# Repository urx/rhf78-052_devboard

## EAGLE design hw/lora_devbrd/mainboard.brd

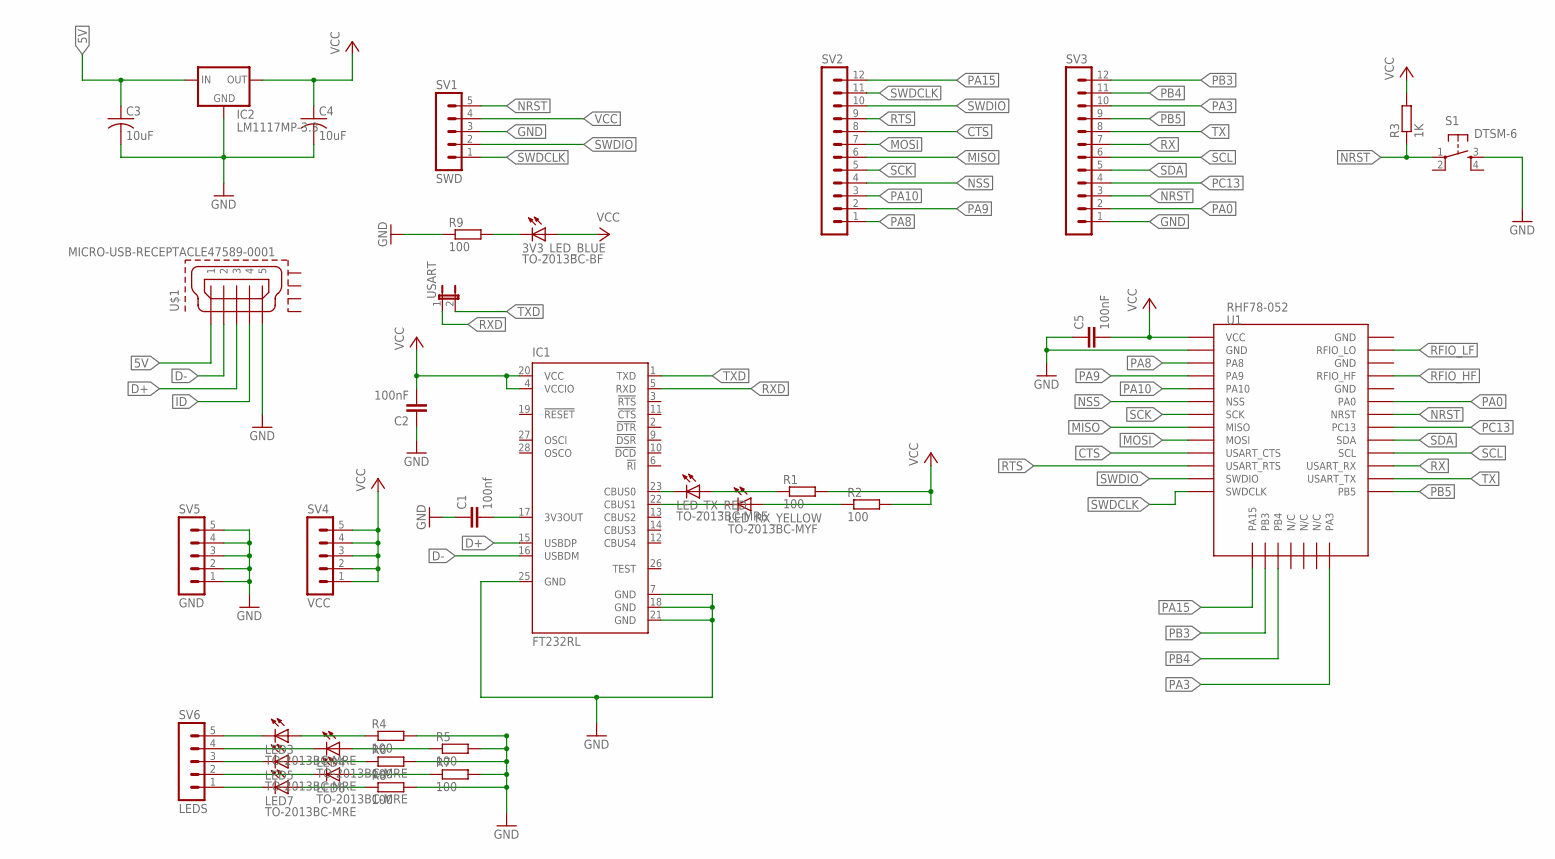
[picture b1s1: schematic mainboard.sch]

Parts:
3V3_LED_BLUE: TO-2013BC-BF; CHIPLED_1206
C1: 100nf; C1206
C2, C5: 100nF; C1206
C3, C4: 10uF; C1206
IC1: FT232RL; SSOP28
IC2: LM1117MP-3.3; SOT223
LED3, LED4, LED5, LED6, LED7: TO-2013BC-MRE; CHIPLED_1206
LED_RX_YELLOW: TO-2013BC-MYF; CHIPLED_1206
LED_TX_RED: TO-2013BC-MRE; CHIPLED_1206
R1, R2, R4, R5, R6, R7, R8, R9: 100; R1206
R3: 1K; R1206
S1: DTSM-6
SV1: SWD; MA05-1
SV2, SV3: MA12-1
SV4: VCC; MA05-1
SV5: GND; MA05-1
SV6: LEDS; MA05-1
U1: RHF78-052
U$1: MICRO-USB-RECEPTACLE47589-0001; 47589-0001
USART: JP1E; JP1

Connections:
3V3OUT: C1.2, IC1.17 (3V3OUT)
5V: C3.1, IC2.3 (IN), U$1.1
CBUS0: IC1.23 (CBUS0), LED_TX_RED.C
CBUS1: IC1.22 (CBUS1), LED_RX_YELLOW.C
CTS: SV2.8, U1.USART_CTS
D+: IC1.15 (USBDP), U$1.3
D-: IC1.16 (USBDM), U$1.2
GND: C1.1, C2.1, C3.2, C4.2, C5.1, IC1.7 (GND), IC1.18 (GND), IC1.21 (GND), IC1.25 (GND), IC2.1 (GND), R4.2, R5.2, R6.2, R7.2, R8.2, R9.1, S1.3, SV1.3, SV3.1, SV5.1, SV5.2, SV5.3, SV5.4, SV5.5, U1.GND@1 (GND), U1.GND@2 (GND), U1.GND@3 (GND), U1.GND@4 (GND), U$1.5
ID: U$1.4
MISO: SV2.6, U1.MISO
MOSI: SV2.7, U1.MOSI
unnamed: 3V3_LED_BLUE.C, R9.2
unnamed: LED_TX_RED.A, R1.1
unnamed: LED_RX_YELLOW.A, R2.1
unnamed: LED3.C, SV6.5
unnamed: LED4.C, SV6.4
unnamed: LED5.C, SV6.3
unnamed: LED6.C, SV6.2
unnamed: LED7.C, SV6.1
unnamed: LED3.A, R4.1
unnamed: LED4.A, R5.1
unnamed: LED5.A, R6.1
unnamed: LED6.A, R7.1
unnamed: LED7.A, R8.1
NRST: R3.1, S1.1, SV1.5, SV3.3, U1.NRST
NSS: SV2.4, U1.NSS
PA0: SV3.2, U1.PA0
PA3: SV3.10, U1.PA3
PA8: SV2.1, U1.PA8
PA9: SV2.2, U1.PA9
PA10: SV2.3, U1.PA10
PA15: SV2.12, U1.PA15
PB3: SV3.12, U1.PB3
PB4: SV3.11, U1.PB4
PB5: SV3.9, U1.PB5
PC13: SV3.4, U1.PC13
RFIO_HF: U1.RFIO_HF
RFIO_LF: U1.RFIO_LF (RFIO_LO)
RTS: SV2.9, U1.USART_RTS
RX: SV3.7, U1.USART_RX
RXD: IC1.5 (RXD), USART.1
SCK: SV2.5, U1.SCK
SCL: SV3.6, U1.SCL
SDA: SV3.5, U1.SDA
SWDCLK: SV1.1, SV2.11, U1.SWDCLK
SWDIO: SV1.2, SV2.10, U1.SWDIO
TX: SV3.8, U1.USART_TX
TXD: IC1.1 (TXD), USART.2
VCC: 3V3_LED_BLUE.A, C2.2, C4.1, C5.2, IC1.4 (VCCIO), IC1.20 (VCC), IC2.2 (OUT), IC2.4 (OUT), R1.2, R2.2, R3.2, SV1.4, SV4.1, SV4.2, SV4.3, SV4.4, SV4.5, U1.VCC

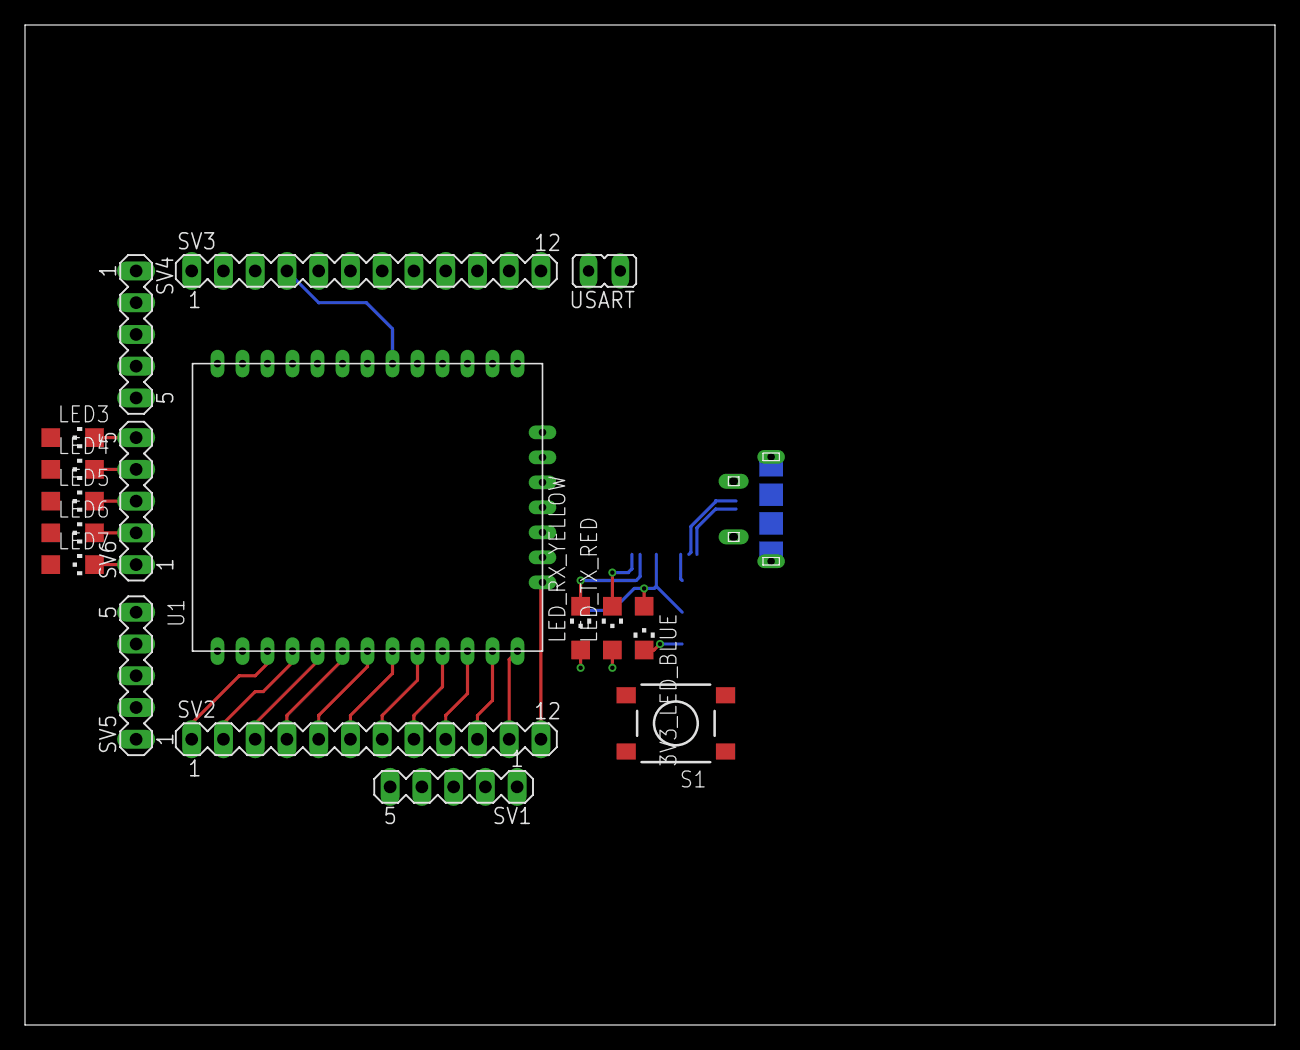
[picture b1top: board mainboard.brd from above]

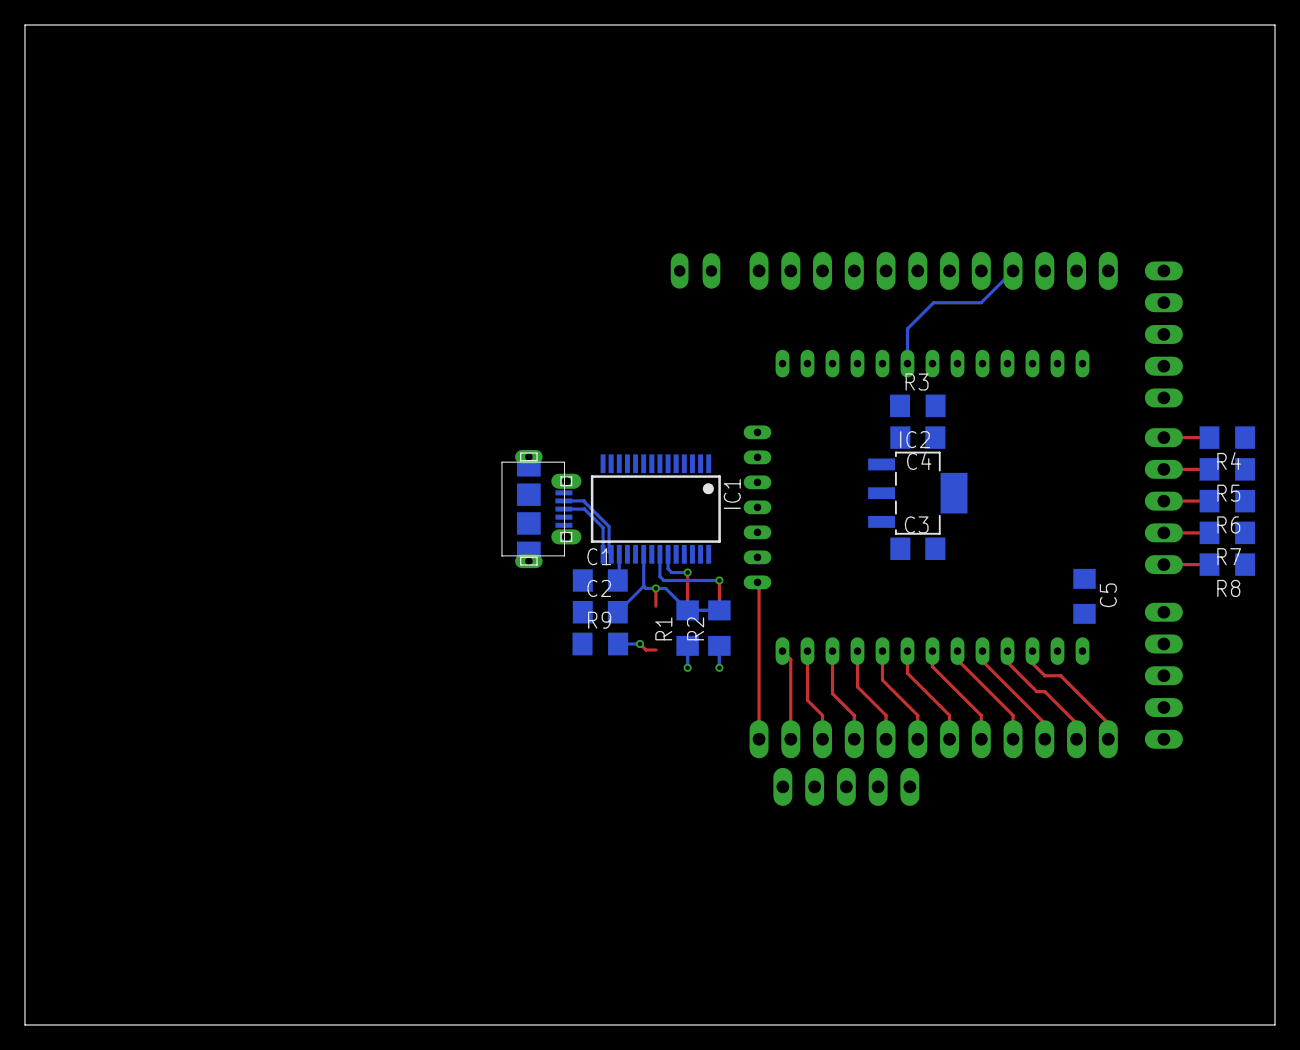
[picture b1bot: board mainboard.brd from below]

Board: 2 copper layers, 100.0 x 80.0 mm, 34 parts (17 on the bottom side), 46 nets.

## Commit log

2019-09-16 RHF78-052 docs
2019-10-21 Initial devboard commit.
    TODO:
    * add 5V -> 3.3V LDO
    * route micro-usb connector
    * add 5V led
    * add 3.3V led
    * add led with pin header for connect to any gpio by wire
2019-10-23 Adds FT232RL
    TODO:
    * add LM1117/SOT-23
    * trace board
    * check, check, check
2019-10-23 Adds LM1117
    TODO:
    * trace board
    * check, check, check
2019-10-23 Adds some leds for power, rx/tx and custom indication
    TODO:
    * trace board
    * check footprints
    * check, check, check
2019-10-23 WIP: tracing
2019-10-28 Switch to github eagle libraries
2019-10-29 WIP: RHF78-052 component
2019-10-29 WIP: RHF78-052 development board
2019-10-29 WIP: [kicad] adds peripherail connectors in schematics
2019-10-29 WIP: [kicad] adds some network names to RHF78-052 pins
2019-10-29 WIP: [kicad] adds ft232rl and some indication led (pwr,rx,tx)
2019-10-30 WIP: [kicad] adds usb connector, lm1117, custom indication leds, pwr and gnd connectors
2019-10-30 WIP: [kicad] ERC OK
2019-10-30 WIP: [kicad] adds yellow and green leds for TX/RX indication
2019-10-30 WIP: [kicad] adds rhf78-052-lcc footprint
2019-11-01 FEAT: [kicad] finished footprint of RHF78-052_LCC
2019-11-04 WIP: added new footprints, sch updated, pcb updated, components placed
2019-11-04 MISC: adds gitignore file
2019-11-05 MISC: [kicad] adds reset button and resistor on SWDIO and SWCLK lines
2019-11-05 MISC: [kicad] sets top layer componetns to it's places
2019-11-05 WIP: [kicad] changed footprints for R and C to 1206
2019-11-06 WIP: [kicad] Components and designators are placed finally
2019-11-06 SX1278 datasheet
2019-11-06 WIP: [kicad] Routed; antennas will be added yet
2019-11-06 MISC: [kicad] updates gitignore file
2019-11-07 WIP: [kicad] adds antennas, routing
2019-11-07 WIP: [kicad] Routing, adds polygons and vias
2019-11-08 FEAT: [kicad] DIY PCB is ready
2019-11-08 FEAT: [kicad] PCB is ready
2019-11-08 FEAT: [kicad] removes misplaced via, removes some unneeded gnd routes
2019-11-08 MISC: [kicad] add some nice writings ^_^
2019-11-09 FEAT: switch to KiCAD
2019-12-06 MISC: added a BOM ordered with ChipDip
2019-12-08 FEAT: adds openocd config
2020-01-01 simple blinker app

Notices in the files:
parts and their libraries:
con-molex-usb: (C) 2014 Tomasz Boleslaw CEDRO, cederom@tlen.pl, http://www.tomek.cedro.info.
